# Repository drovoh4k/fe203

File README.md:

# Fe203

Dashboard PCB for a Formula Student Car

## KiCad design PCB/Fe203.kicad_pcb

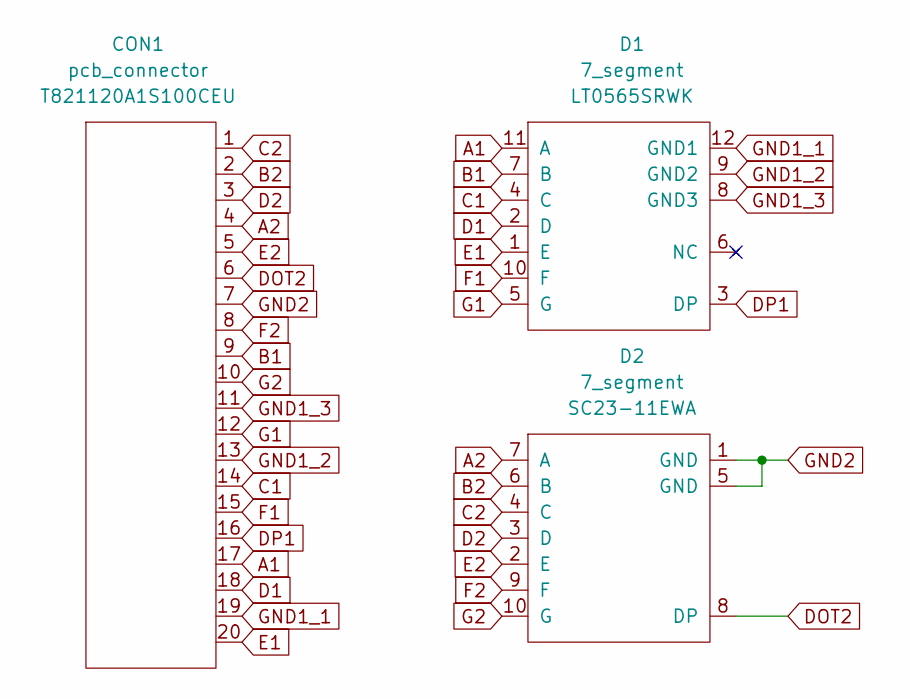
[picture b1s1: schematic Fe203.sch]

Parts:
CON1: pcb_connector; 20_pin_pcb_connector
D1: 7_segment; LT0565SRWK
D2: 7_segment; SC23-11EWA

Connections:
A1: CON1.17, D1.11 (A)
A2: CON1.4, D2.7 (A)
B1: CON1.9, D1.7 (B)
B2: CON1.2, D2.6 (B)
C1: CON1.14, D1.4 (C)
C2: CON1.1, D2.4 (C)
D1: CON1.18, D1.2 (D)
D2: CON1.3, D2.3 (D)
DOT2: CON1.6, D2.8 (DP)
DP1: CON1.16, D1.3 (DP)
E1: CON1.20, D1.1 (E)
E2: CON1.5, D2.2 (E)
F1: CON1.15, D1.10 (F)
F2: CON1.8, D2.9 (F)
G1: CON1.12, D1.5 (G)
G2: CON1.10, D2.10 (G)
GND1_1: CON1.19, D1.12 (GND1)
GND1_2: CON1.13, D1.9 (GND2)
GND1_3: CON1.11, D1.8 (GND3)
GND2: CON1.7, D2.1 (GND), D2.5 (GND)

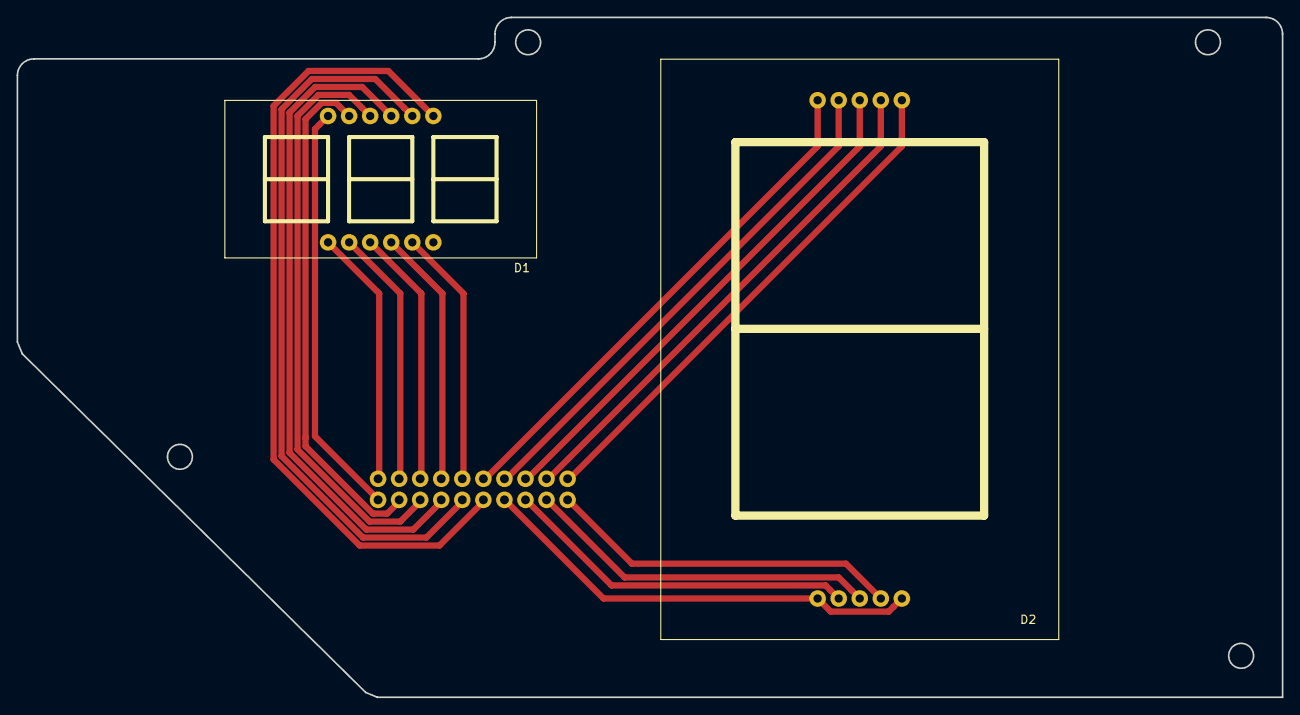
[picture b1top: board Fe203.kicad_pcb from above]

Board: 2 copper layers, 152.6 x 82.0 mm, 3 parts (1 on the bottom side), 20 nets.

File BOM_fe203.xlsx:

ID | Ref placa | Fabricant | Ref fabricant | Descripció | Preu unitat | Unitats | Preu total
1.0 | CON1 | AMPHENOL | T821120A1S100CEU | Connector placa 20 contactos | 0.27 | 1.0 | 0.27
2.0 | D1 | MULTICOMP PRO | LT0565SRWK | Triple 7 segment | 2.26 | 1.0 | 2.26
3.0 | D2 | KINGBRIGHT | SC23-11EWA | Single 7 segment | 7.77 | 1.0 | 7.77
4.0 | WIRE 1 | AMPHENOL | FC20150-0 | Cable plano 20 contactos | 3.23 | 1.0 | 3.23
 |  | Preu total sense IVA | 13.53
 |  | IVA | 0.21
 |  | Preu total amb IVA | 16.3713

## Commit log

2021-02-02 README.md removed
